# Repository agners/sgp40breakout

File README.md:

# SGP40 & SHT35-DIS Breakout Board

Simple Breakout Board for Sensirion SGP40 (VOC Sensor) and SHT35-DIS (Temperature
and Humidity Sensor). A PDF version of the schematic: [sgp40breakout.pdf](sgp40breakout.pdf).

Designed with KiCad.

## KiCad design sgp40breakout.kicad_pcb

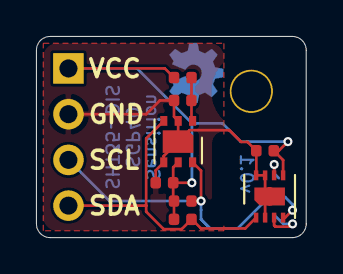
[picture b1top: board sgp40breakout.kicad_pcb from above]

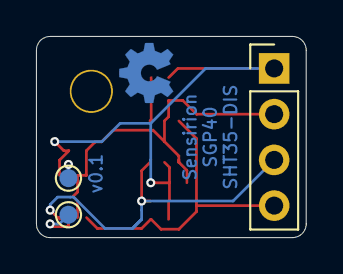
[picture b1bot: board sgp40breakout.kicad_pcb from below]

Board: 2 copper layers, 15.0 x 11.2 mm, 12 parts (3 on the bottom side), 7 nets.

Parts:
C1, C2: 1µF; C_0402_1005Metric
C3: 100nF; C_0402_1005Metric
H1: MountingHole; MountingHole_2.2mm_M2_Pad
J1: Conn_01x04_Male; PinHeader_1x04_P2.54mm_Vertical
R1: 4.7Ω; R_0402_1005Metric
R2, R3: 4.7kΩ; R_0402_1005Metric
TP1, TP2: TestPoint; TestPoint_Pad_D1.0mm
U1: SGP40; Sensirion_DFN-6-1EP_2.44x2.44mm_P0.8mm
U2: SHT35-DIS; Sensirion_DFN-8-1EP_2.5x2.5mm_P0.5mm_EP1.1x1.7mm

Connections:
GND: C1.1, C2.1, C3.1, J1.2, U1.2, U1.4, U1.7, U2.2, U2.7, U2.8, U2.9
unnamed: C1.2, R1.2, U1.1
unnamed: TP1.1, U2.6
unnamed: TP2.1, U2.3
SCL: J1.3, R2.2, U1.6, U2.4
SDA: J1.4, R3.2, U1.3, U2.1
VCC: C2.2, C3.2, J1.1, R1.1, R2.1, R3.1, U1.5, U2.5

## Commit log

2020-10-02 initial board layout
    Board Layout for OSH Park manufacturing service.
2020-10-02 add .gitignore
2020-10-03 add missing file, fix back silk screen
2020-10-03 remove most gold plating from mounting hole
2020-10-03 add OSHW logo
2020-10-03 assign 3D models and flip mount side of pin header
    Using KiCad nightly...
2020-10-03 revert back to stable KiCad PCB
    Convert sgp40breakout.kicad_pcb back to a format readable by the stable
    version of KiCad. Move pin header to the back using stable version.
2020-10-03 move testpoints in Schema to not intersect with other elements
    Just a cosmetic change.
2020-10-03 add pictures and schema
2020-10-03 move front silkscreen text a bit closer to the soldering pads
2020-10-03 increase milling slit to 5mm
2020-10-03 update SGP40 symbol

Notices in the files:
sgp40breakout.kicad_pcb:
License: BSD 2-Clause
